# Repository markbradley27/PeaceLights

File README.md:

PeaceLights
===========

PeaceLights is secret... for now.

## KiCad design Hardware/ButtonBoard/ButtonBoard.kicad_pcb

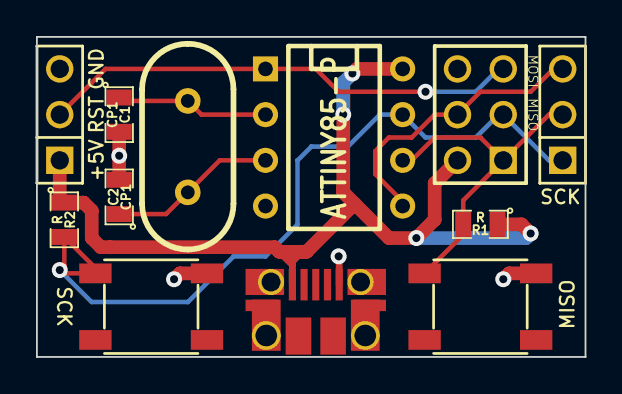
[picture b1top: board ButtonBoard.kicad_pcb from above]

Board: 2 copper layers, 30.5 x 17.8 mm, 6 parts (0 on the bottom side), 4 nets.

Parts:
C1, C2: CP1; SM0805
R1, R2: R; SM0805
SW1, SW2: SW_PUSH; SWITCH-ALPS

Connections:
+5V: R1.1, R2.1
/MISO: R1.2, SW1.1
/SCK: R2.2, SW2.1
GND: C1.2, C2.2, SW1.2, SW2.2

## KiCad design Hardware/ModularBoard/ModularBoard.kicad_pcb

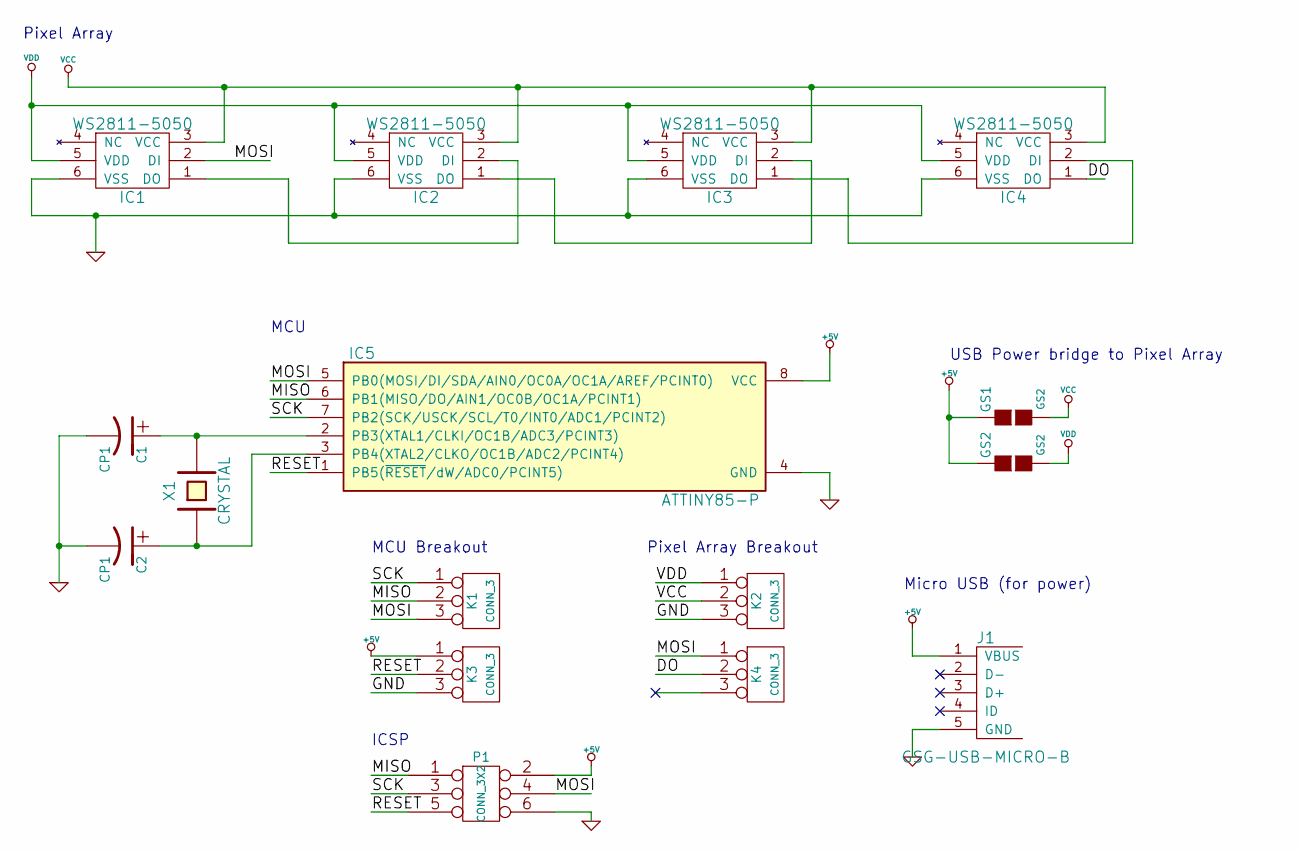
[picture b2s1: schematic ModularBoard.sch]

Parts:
C1, C2: CP1
GS1, GS2: GS2
IC1, IC2, IC3, IC4: WS2811-5050
IC5: ATTINY85-P; DIP8
J1: GSG-USB-MICRO-B
K1, K2, K3, K4: CONN_3
P1: CONN_3X2
X1: CRYSTAL

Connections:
+5V: GS1.1 (G1), GS2.1 (G1), IC5.8 (VCC), J1.1 (VBUS), K3.1, P1.2
/DO: IC4.1 (DO), K4.2 (PM)
/MISO: IC5.6 (PB1(MISO/DO/AIN1/OC0B/OC1A/PCINT1)), K1.2 (PM), P1.1
/MOSI: IC1.2 (DI), IC5.5 (PB0(MOSI/DI/SDA/AIN0/OC0A/OC1A/AREF/PCI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), K1.3, K4.1, P1.4
/RESET: IC5.1 (PB5(~RESET~/dW/ADC0/PCINT5)), K3.2 (PM), P1.5
/SCK: IC5.7 (PB2(SCK/USCK/SCL/T0/INT0/ADC1/PCINT2)), K1.1, P1.3
GND: C1.2, C2.2, IC1.6 (VSS), IC2.6 (VSS), IC3.6 (VSS), IC4.6 (VSS), IC5.4 (GND), J1.5 (GND), K2.3, K3.3, P1.6
unnamed: IC1.1 (DO), IC2.2 (DI)
unnamed: IC2.1 (DO), IC3.2 (DI)
unnamed: IC3.1 (DO), IC4.2 (DI)
unnamed: C1.1, IC5.2 (PB3(XTAL1/CLKI/OC1B/ADC3/PCINT3)), X1.2
unnamed: C2.1, IC5.3 (PB4(XTAL2/CLKO/OC1B/ADC2/PCINT4)), X1.1
VCC: GS1.2 (G2), IC1.3 (VCC), IC2.3 (VCC), IC3.3 (VCC), IC4.3 (VCC), K2.2 (PM)
VDD: GS2.2 (G2), IC1.5 (VDD), IC2.5 (VDD), IC3.5 (VDD), IC4.5 (VDD), K2.1

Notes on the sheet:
Pixel Array
MCU Breakout
Pixel Array Breakout
ICSP
Micro USB (for power)
USB Power bridge to Pixel Array
MCU

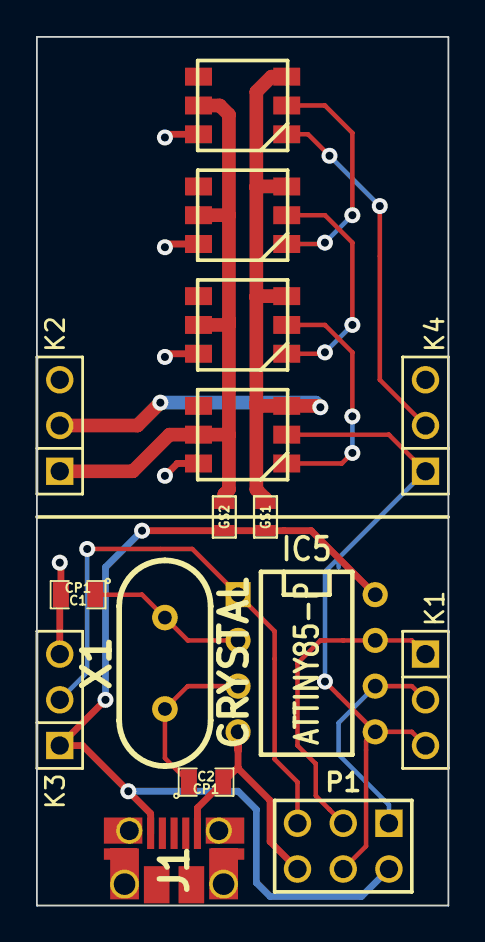
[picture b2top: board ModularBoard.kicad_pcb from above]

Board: 2 copper layers, 22.9 x 48.3 mm, 16 parts (0 on the bottom side), 14 nets.

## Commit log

2013-08-14 Project initialization
2013-08-14 Complete board with just MCU and USB port
2013-08-14 Fixed derpy USB port, now micro instead of mini
2013-08-15 Updated schematic, should just need a few more breakout pins, maybe caps for filtering
2013-08-17 Schematic should be done, board partially implemented
2013-08-17 board should be done, save trace width tweaking
2013-08-18 Made the board more compact, might do more by putting ICSP and USB side by side
2013-08-18 Fixed ICSP header
2013-08-18 saved project
2013-08-18 Its compact! Fits in 5x5cm square
2013-08-18 made sure ground was all connected
2013-08-18 added a bit of space between MCU and ICSP header, ground plane fills better now
2013-08-19 Switched crystal caps to 0805
2013-08-19 Rendered gerber files, ordered from OSHPark!
2013-09-05 date update
2013-09-05 Functioning blink test, downloaded WS2811 code
2013-09-06 Working code for modular board
2013-09-09 Added pixel brakout boards
2013-09-10 tinkering with code
2013-09-10 Created new board with two buttons, hopefully the final product
2013-09-30 All the code!
